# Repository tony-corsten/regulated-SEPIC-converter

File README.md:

# regulated-SEPIC-converter
# Overview
The ADP5070/5071 are integrated dual rail switching power supplies that can generate outputs of up to -39V - 39V from an input voltage of 2.85V - 15V. As an alternative to low current charge pumps, the ADP5071 is specced to deliver up to 2A on the positive rail and 1.2A on the negative rail (compared to ~50-100mV out of a typical charge pump). This makes it great for use in a system requiring high current dual rail inputs, like high-power op amps or ADCs.

Additionally, the chip has flexibility in what kind of switching architecture is employed. Typically, the chip operates in a boost architecture, and the inverting converter works on the boosted voltage. However, the chip can also employ a modern SEPIC design, where the chip can either boost *OR* buck automatically based on the board configuration. **The current configuration of the board is as a SEPIC converter.** There are two LDOs (one for each rail) at the output to regulate the output as well. _Note that the selected LDOs (LT3094 and LT3042/4) are only specced for 500mA on each regulator_. If you don't require low-noise, but do require high current, I recommend changing these out for higher current LDOs!

You can find the official documentation for the [ADP5071 chip here,](https://www.analog.com/en/products/adp5071.html) for the [LT3094 here,](https://www.analog.com/en/products/lt3094.html) and for [the LT3045 here](https://www.analog.com/en/products/lt3045.html#product-overview). This is a breakout board made in Kicad with a barrel jack power input [(the PJ-037A)](https://www.digikey.com/product-detail/en/cui-inc/PJ-037A/CP-037A-ND/1644545) and [SMA connectors for each output](https://www.amazon.com/gp/product/B00G94UK74/ref=ppx_yo_dt_b_search_asin_title?ie=UTF8&psc=1) (+/- rail for switching supply, and +/- rail for LDOs).

*_Note_*: The board is currently designed for a +/- 6V rail for a 9V battery input, which *only* works in a SEPIC design. If not using the SEPIC design, make sure to have the desired positive rail be higher than the input voltage. 

# Navigating this repo
The main folder contains relevant Kicad files (.pro, .pcb, .sch). The `gerber` directory has a PCB-fabrication ready set of gerber files. The `library` directory contains a custom kicad footprint for the PJ-037A, SMA connector and LPD3015 power inductor. There are also hand-solderable footprints for the linear regulators included. Finally, an updated `devices` library is available for the symbol for the LPD3015 (alternatively, you can make the symbol yourself as a small edit to the existing coupled inductor). 

# Board images
PCB Layout:

Schematic:

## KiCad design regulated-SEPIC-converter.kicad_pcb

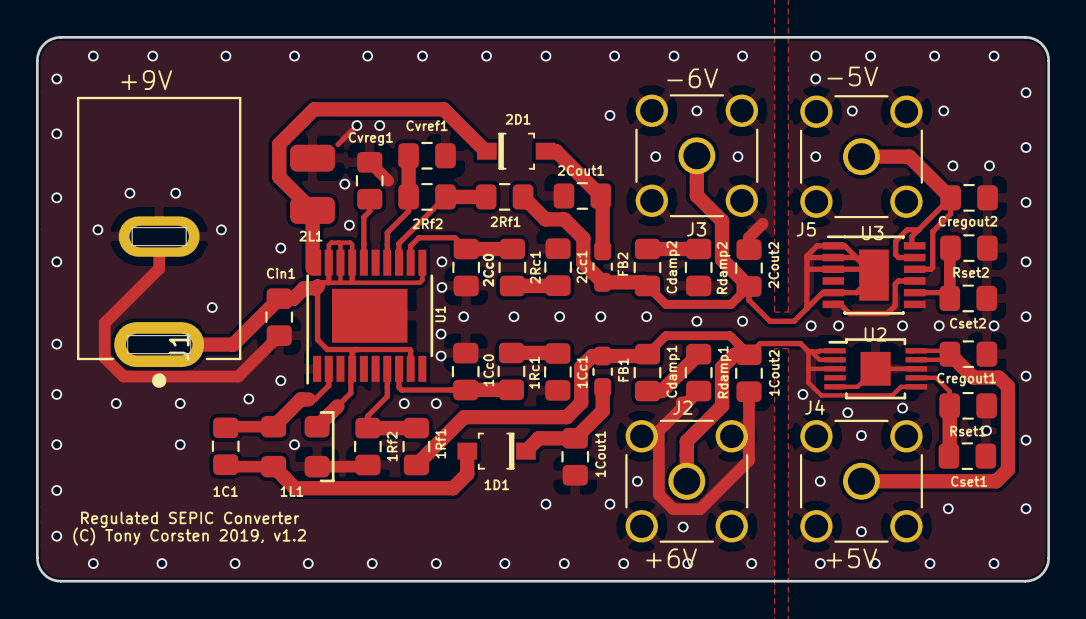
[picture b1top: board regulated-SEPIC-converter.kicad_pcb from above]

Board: 2 copper layers, 56.2 x 30.2 mm, 42 parts (0 on the bottom side), 23 nets.

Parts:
1C1: 1uF; C_0805_2012Metric_Pad1.15x1.40mm_HandSolder
1Cc0, 2Cc0: 47pF; C_0805_2012Metric_Pad1.15x1.40mm_HandSolder
1Cc1: 8.2nF; C_0805_2012Metric_Pad1.15x1.40mm_HandSolder
1Cout1, 2Cout1: 10uF; C_0805_2012Metric_Pad1.15x1.40mm_HandSolder
1Cout2, 2Cout2: 10nF; C_0805_2012Metric_Pad1.15x1.40mm_HandSolder
1D1, 2D1: MBR0520LT1G; SOD-123_UPDATED
1L1: LPD3015-222; LPD3015
1Rc1: 7.32K; R_0805_2012Metric_Pad1.15x1.40mm_HandSolder
1Rf1: 84.5K; R_0805_2012Metric_Pad1.15x1.40mm_HandSolder
1Rf2: 13K; R_0805_2012Metric_Pad1.15x1.40mm_HandSolder
2Cc1: 6.8nF; C_0805_2012Metric_Pad1.15x1.40mm_HandSolder
2L1: 4.7uH; LQH32PN4R7NN0
2Rc1: 7.68K; R_0805_2012Metric_Pad1.15x1.40mm_HandSolder
2Rf1: 90.9K; R_0805_2012Metric_Pad1.15x1.40mm_HandSolder
2Rf2: 10.7K; R_0805_2012Metric_Pad1.15x1.40mm_HandSolder
Cdamp1, Cdamp2: 1uF; C_0805_2012Metric_Pad1.15x1.40mm_HandSolder
Cin1: 10uF; C_0805_2012Metric_Pad1.15x1.40mm_HandSolder
Cregout1: 4.7uF; C_0805_2012Metric_Pad1.15x1.40mm_HandSolder
Cregout2: 10uF; C_0805_2012Metric_Pad1.15x1.40mm_HandSolder
Cset1: 0.47uF; C_0805_2012Metric_Pad1.15x1.40mm_HandSolder
Cset2: 4.7uF; C_0805_2012Metric_Pad1.15x1.40mm_HandSolder
Cvref1: 1uF; C_0805_2012Metric_Pad1.15x1.40mm_HandSolder
Cvreg1: 1uF; C_0805_2012Metric_Pad1.15x1.40mm_HandSolder
FB1, FB2: MPZ1608S101A; R_0603_1608Metric_Pad1.05x0.95mm_HandSolder
J1: Barrel_Jack; PJ-037A
J2, J3, J4, J5: Conn_Coaxial; SMA_Vertical_Connector
Rdamp1, Rdamp2: 2.0; R_0805_2012Metric_Pad1.15x1.40mm_HandSolder
Rset1, Rset2: 49.9K; R_0805_2012Metric_Pad1.15x1.40mm_HandSolder
U1: ADP5071AREZ; ETSSOP-20-1EP_4.4x6.5mm_P0.65mm_EP3x4.2mm
U2: LT3042EMSE-PBF; MSOP-10-1EP_3x3mm_P0.5mm_EP1.68x1.88mm_HAND_SOLDER
U3: LT3094EMSE; MSOP-12-1EP_3x4mm_P0.65mm_EP1.65x2.85mm_HAND_SOLDER

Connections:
+3V3: 1L1.1, Cin1.1, J1.1, U1.4, U1.9, U1.11, U1.17, U1.18, U1.19
+5V: Cregout1.2, J4.1, U2.9, U2.10
+6V: 1Cout2.1, 1Rf1.1, Cdamp1.1, FB1.1, J2.1, U2.1, U2.2, U2.3, U2.6
-5V: Cregout2.2, J5.1, U3.10, U3.11, U3.12
-6V: 2Cout2.2, 2Rf1.1, Cdamp2.2, FB2.1, J3.1, U3.1, U3.2, U3.3, U3.5, U3.13
/COMP1: 1Cc0.2, 1Rc1.1, U1.8
/COMP2: 2Cc0.2, 2Rc1.1, U1.12
/FB1: 1Rf1.2, 1Rf2.2, U1.7
/FB2: 2Rf1.2, 2Rf2.2, U1.13
/SW1: 1C1.1, 1L1.2, U1.2
/SW2: 2D1.K, 2L1.1, U1.20
/VREF: 2Rf2.1, Cvref1.1, U1.14
/VREG: Cvreg1.2, U1.16
GND: 1Cc0.1, 1Cc1.1, 1Cout1.2, 1Cout2.2, 1L1.4, 1Rf2.1, 2Cc0.1, 2Cc1.1, 2Cout1.1, 2Cout2.1, 2L1.2, Cin1.2, Cregout1.1, Cregout2.1, Cset1.2, Cset2.2, Cvref1.2, Cvreg1.1, J1.2, J2.2, J3.2, J4.2, J5.2, Rdamp1.2, Rdamp2.1, Rset1.2, Rset2.2, U1.1, U1.6, U1.15, U1.21, U2.5, U2.8, U2.11, U3.6, U3.9
unnamed: 1C1.2, 1D1.A, 1L1.3
unnamed: 1Cc1.2, 1Rc1.2
unnamed: 1Cout1.1, 1D1.K, FB1.2
unnamed: 2Cc1.2, 2Rc1.2
unnamed: 2Cout1.2, 2D1.A, FB2.2
unnamed: Cdamp1.2, Rdamp1.1
unnamed: Cdamp2.1, Rdamp2.2
unnamed: Cset1.1, Rset1.1, U2.7
unnamed: Cset2.1, Rset2.1, U3.8
